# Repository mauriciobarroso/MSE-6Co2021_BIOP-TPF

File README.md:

# MSE-6Co2021_BIOP-TPF
Trabajo Práctico Final para la materia Biopotenciales y Signos Vitales, Registros y Aplicaciones

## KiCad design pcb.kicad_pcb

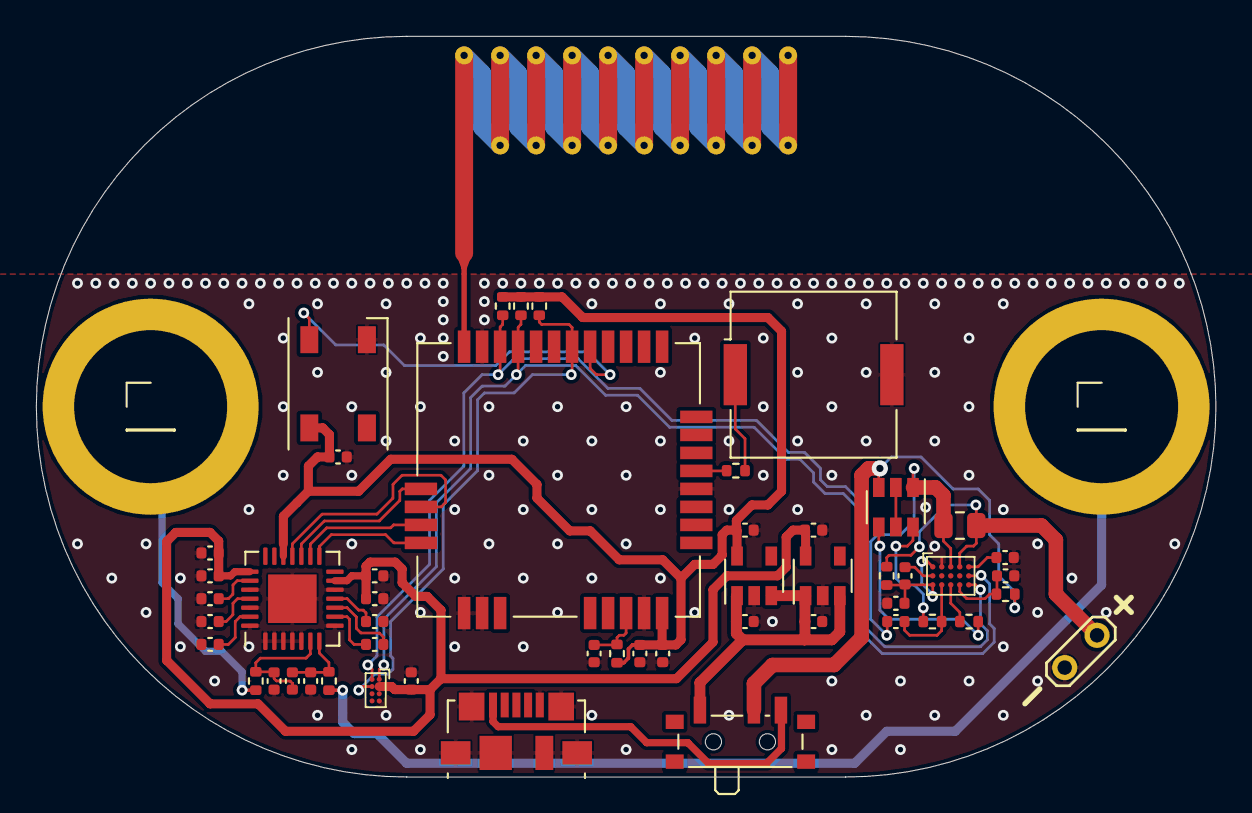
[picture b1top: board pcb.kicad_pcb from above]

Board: 2 copper layers, 65.5 x 41.1 mm, 53 parts (0 on the bottom side), 39 nets.

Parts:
AE1: Antenna; Texas_SWRA416_868MHz_915MHz
BT1: Battery; TestPoint_2Pads_Pitch2.54mm_Drill0.8mm
BZ1: Buzzer; Buzzer_Murata_PKMCS0909E4000-R1
C1, C3: 10p; C_0402_1005Metric
C2, C7, C9, C10, C20: 10u; C_0402_1005Metric
C4, C6, C8, C11, C14, C15, C16, C17, C23: 1u; C_0402_1005Metric
C5, C12, C25, C26: 1n; C_0402_1005Metric
C13, C18, C19, C22, C24: 100n; C_0402_1005Metric
C21: 470n; C_0402_1005Metric
D4: WS2812B; LED_WS2812B_PLCC4_5.0x5.0mm_P3.2mm
J1: USB_B_Micro; USB_Micro-B_Molex_47346-0001
J2: EGCP_CNN; ECG_3.9mm_Snap_Connector
J3: EGCN_CNN; ECG_3.9mm_Snap_Connector
Q1: DMG9926UDM; SOT-23-6
R1, R2: 49.9K; R_0402_1005Metric
R3: 10; R_0402_1005Metric
R4: 0.01; R_0805_2012Metric
R5: 100; R_0402_1005Metric
R6, R11, R12: 1K; R_0402_1005Metric
R7: 10K; R_0402_1005Metric
R8, R9, R10: 5.1K; R_0402_1005Metric
SW1: SW_SPDT; SW_SPDT_PCM12
U1: MAX30003CTI+; TQFN-28-1EP_5x5mm_P0.5mm_EP2.7x2.7mm
U2: AP2112K-1.8; SOT-23-5
U3: AP2112K-3.3; SOT-23-5
U4: RAK3172
U5: MAX17330X22+; Maxim_WLP-15
U7: SX9210; WLCSP-8_1.69x0.92mm_P0.4mm

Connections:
+1V8: C8.1, C9.1, C10.1, C11.1, C16.1, C24.1, U1.13, U1.22, U2.5, U7.A2
+3V3: C17.1, C19.1, C20.1, C22.1, D4.1, R7.2, R8.2, R9.2, R10.2, U1.19, U3.5, U4.24
+3V8: C14.1, C15.1, SW1.1, U2.1, U2.3, U3.1, U3.3
+BATT: BT1.1, R3.2, R4.2, U5.A4
/BUZZER: R6.2, U4.29
/CHARGER|LOAD: Q1.3, R12.2, SW1.2
/CS: U1.15, U4.16
/ECGN: J2.1, R2.1
/ECGP: J3.1, R1.2
/MISO: U1.18, U4.14
/MOSI: U1.17, U4.13
/NIRQ: R10.1, U4.6, U7.B2
/RGB_LED: D4.4, U4.5
/SCL: R9.1, U4.9, U5.B5, U7.A1
/SCLK: U1.16, U4.15
/SDA: R8.1, U4.10, U5.C5, U7.B1
GND: BT1.2, BZ1.2, C1.2, C2.2, C3.2, C4.2, C7.2, C8.2, C9.2, C10.2, C11.2, C12.2, C13.2, C14.2, C15.2, C16.2, C17.2, C19.2, C20.2, C21.2, C22.2, C23.2, C24.2, C26.2, D4.3, J1.5, J1.6, U1.1, U1.2, U1.3, U1.4, U1.5, U1.8, U1.12, U1.24, U1.26, U1.28, U1.29, U2.2, U3.2, U4.11, U4.17, U4.18, U4.23, U4.28, U5.A2, U7.A4
unnamed: AE1.1, U4.12
unnamed: BZ1.1, R6.1
unnamed: C1.1, C5.2, R2.2, U1.7
unnamed: C2.1, U1.25
unnamed: C3.1, C5.1, R1.1, U1.6
unnamed: C4.1, U1.27
unnamed: C6.1, U1.9
unnamed: C6.2, U1.10
unnamed: C7.1, U1.23
unnamed: C12.1, U1.11
unnamed: C13.1, C18.2, R3.1, U5.A1, U5.C1
unnamed: C18.1, U5.B1
unnamed: C21.1, U5.A5
unnamed: C23.1, R7.1, U4.22
unnamed: C25.1, R5.1, U5.C2
unnamed: C25.2, Q1.1, R4.1, U5.A3
unnamed: C26.1, R12.1, U5.C4
unnamed: Q1.2, Q1.5
unnamed: Q1.4, R11.2
unnamed: Q1.6, R5.2
unnamed: R11.1, U5.C3
VBUS: J1.1, SW1.3

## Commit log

2022-05-15 added first version of the PCB
2022-05-15 added local libraries and footprints
2022-05-15 changed 3d models locations
